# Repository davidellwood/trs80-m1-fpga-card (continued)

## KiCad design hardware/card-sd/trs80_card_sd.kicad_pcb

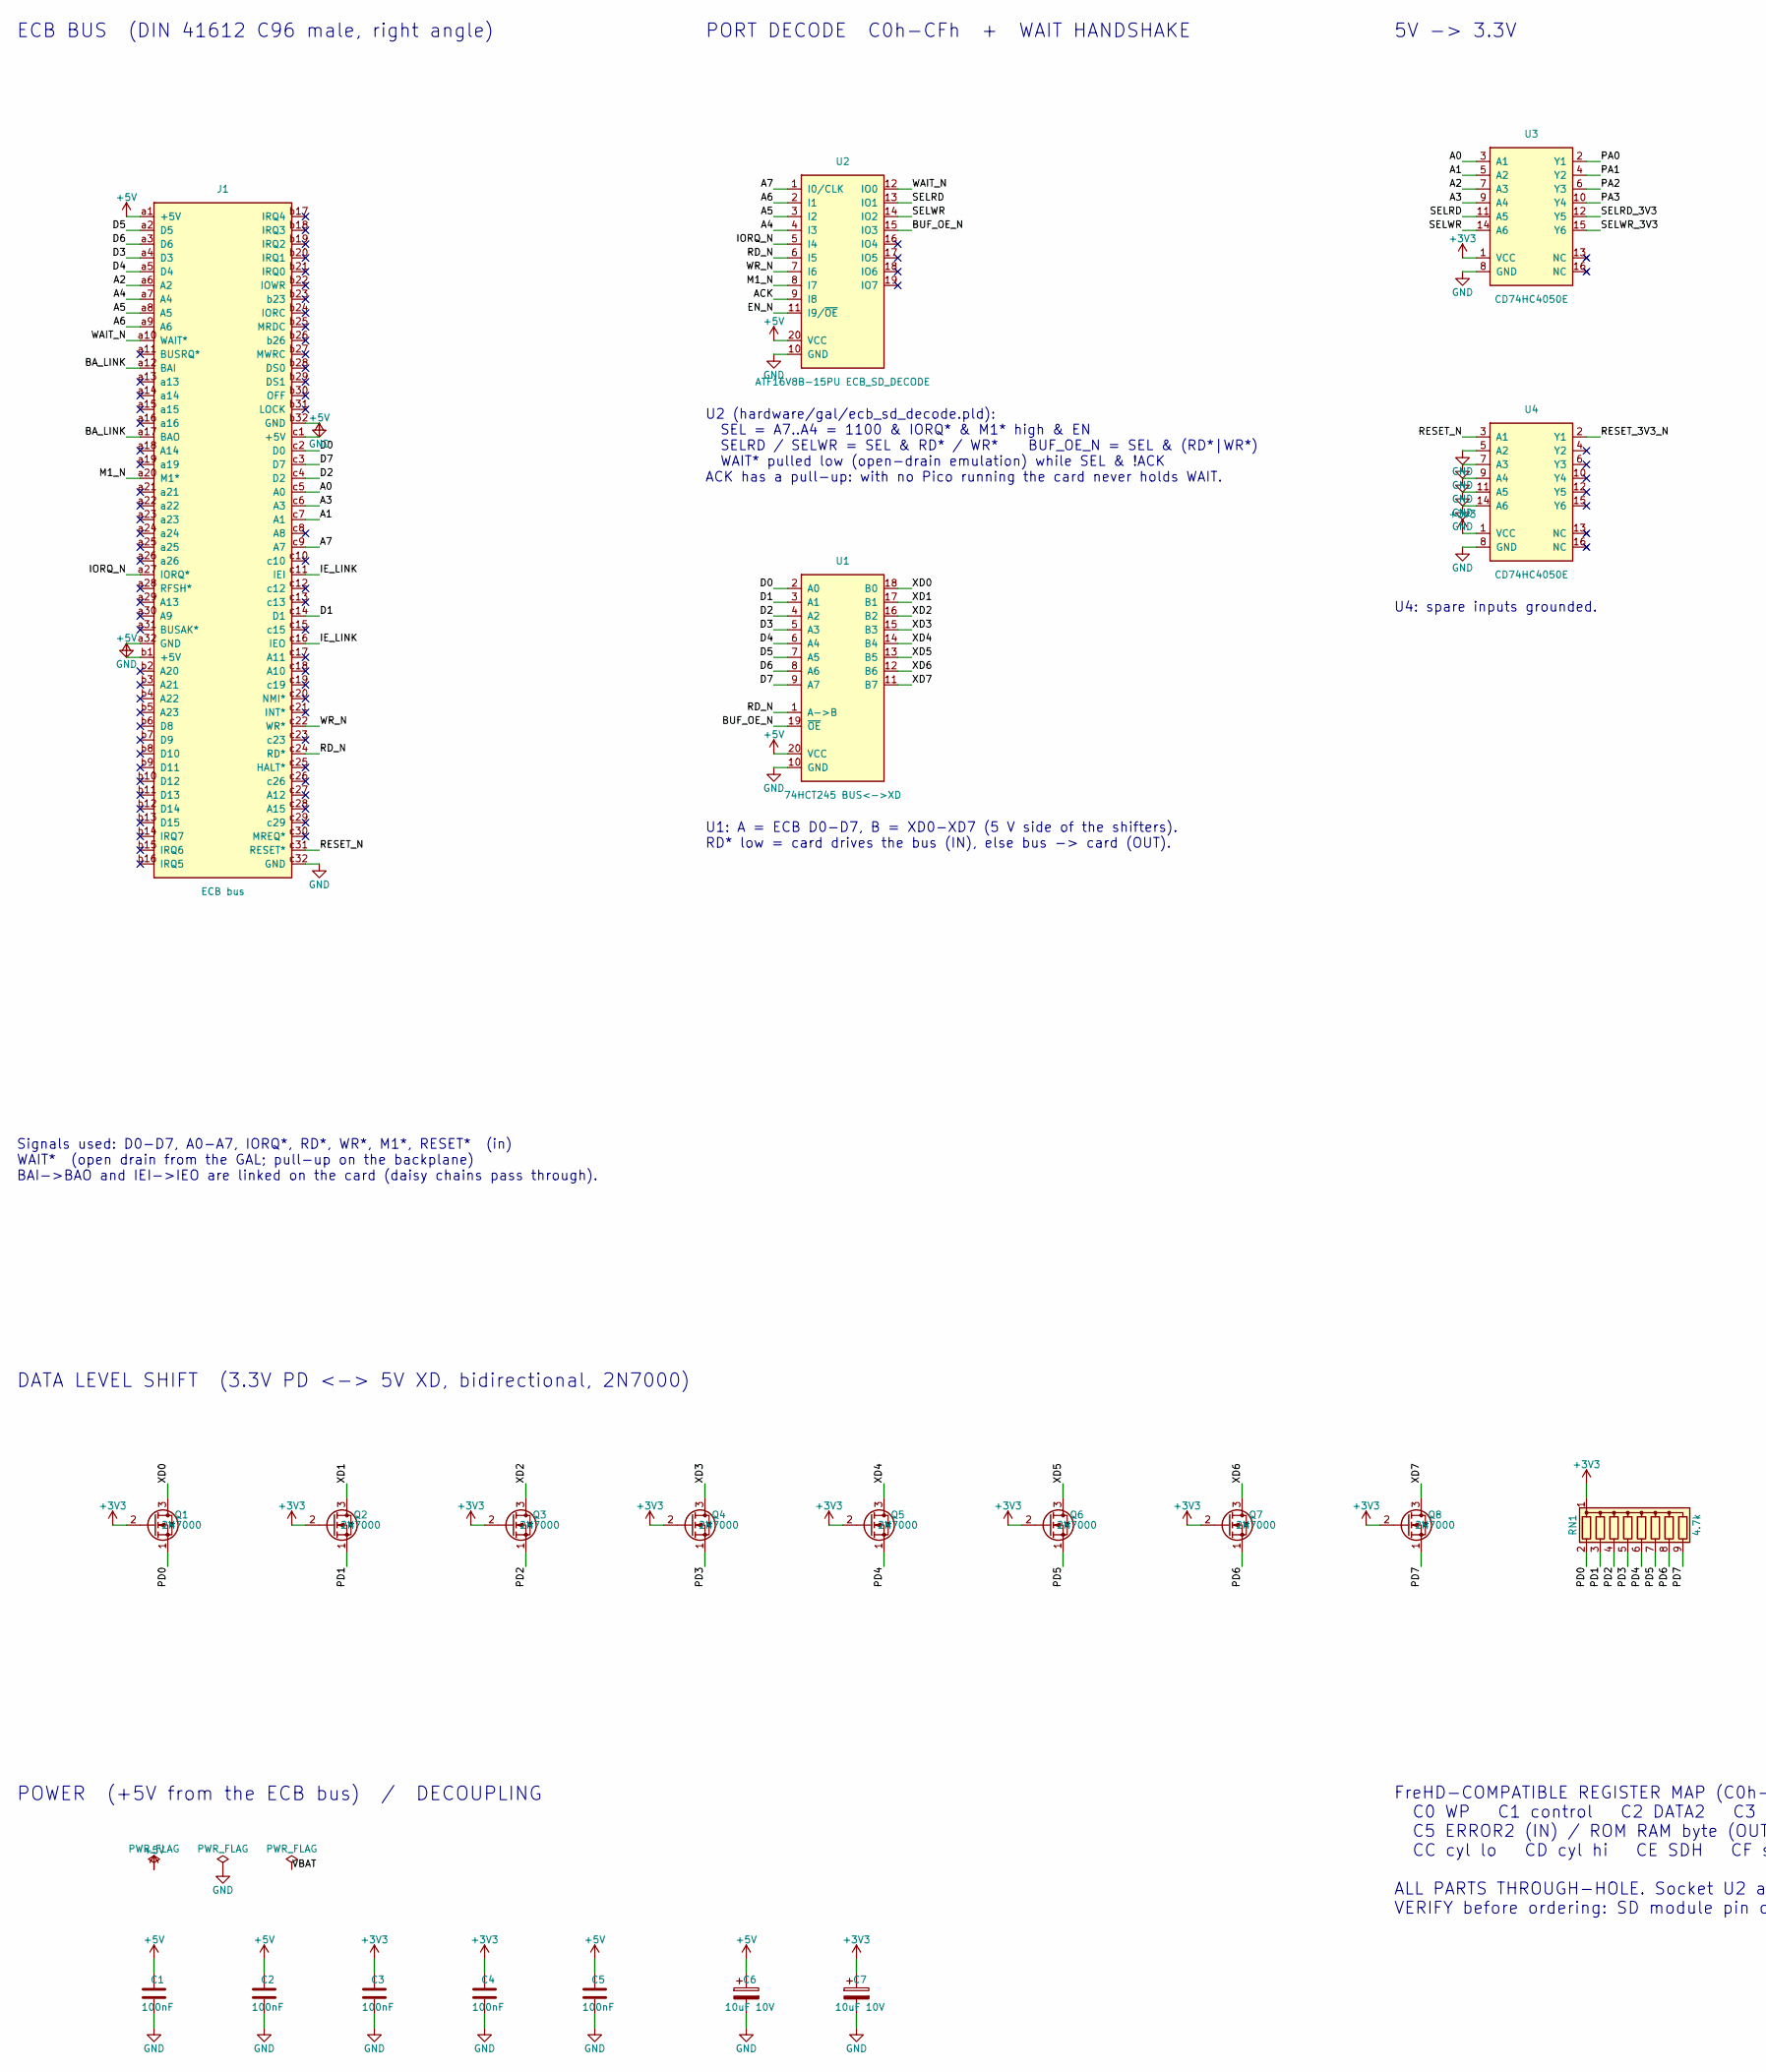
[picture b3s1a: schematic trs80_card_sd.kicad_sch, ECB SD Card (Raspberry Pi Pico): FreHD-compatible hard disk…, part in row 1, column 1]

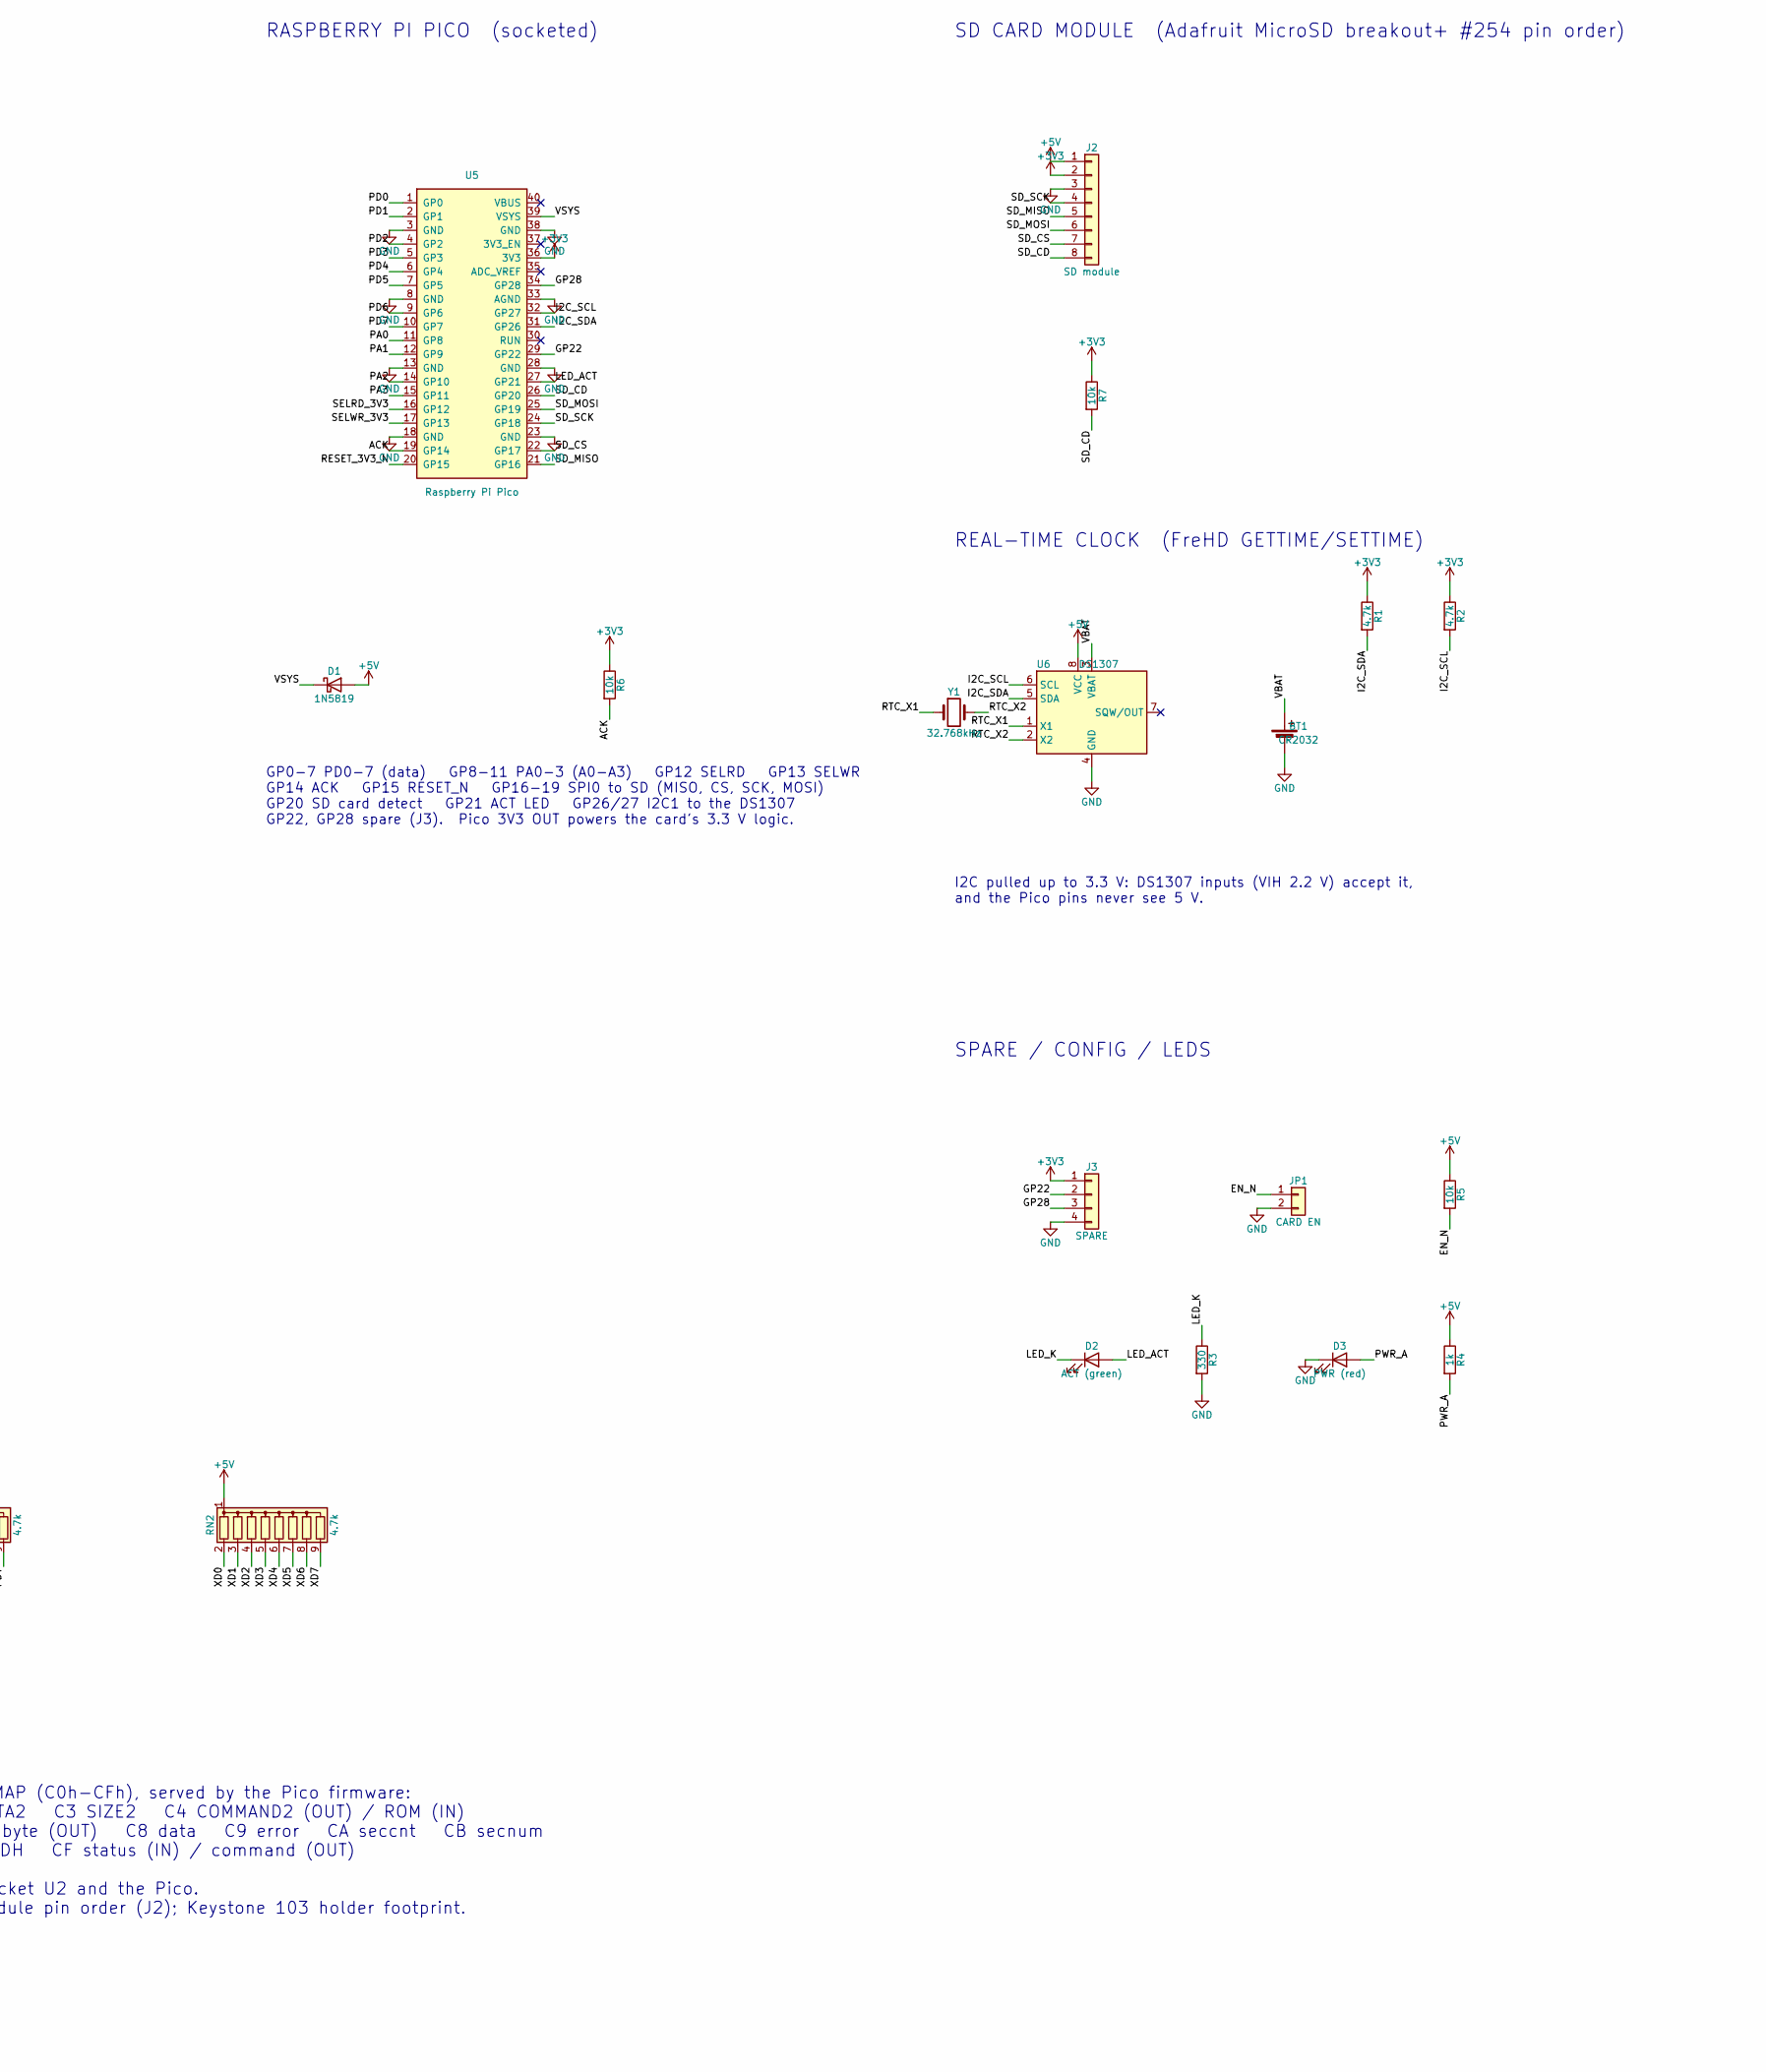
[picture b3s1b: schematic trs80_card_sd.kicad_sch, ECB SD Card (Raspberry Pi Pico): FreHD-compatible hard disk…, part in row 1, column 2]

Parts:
BT1: CR2032; BatteryHolder_Keystone_103_1x20mm
C1, C2, C3, C4, C5: 100nF; C_Disc_D5.0mm_W2.5mm_P5.00mm
C6, C7: 10uF 10V; CP_Radial_D5.0mm_P2.00mm
D1: 1N5819; D_DO-41_SOD81_P10.16mm_Horizontal
D2: ACT (green); LED_D3.0mm
D3: PWR (red); LED_D3.0mm
J1: ECB bus; DIN41612_C_3x32_Male_Horizontal_THT
J2: SD module; PinSocket_1x08_P2.54mm_Vertical
J3: SPARE; PinHeader_1x04_P2.54mm_Vertical
JP1: CARD EN; PinHeader_1x02_P2.54mm_Vertical
Q1, Q2, Q3, Q4, Q5, Q6, Q7, Q8: 2N7000; TO-92_Inline_Wide
R1, R2: 4.7k; R_Axial_DIN0207_L6.3mm_D2.5mm_P10.16mm_Horizontal
R3: 330; R_Axial_DIN0207_L6.3mm_D2.5mm_P10.16mm_Horizontal
R4: 1k; R_Axial_DIN0207_L6.3mm_D2.5mm_P10.16mm_Horizontal
R5, R6, R7: 10k; R_Axial_DIN0207_L6.3mm_D2.5mm_P10.16mm_Horizontal
RN1, RN2: 4.7k; R_Array_SIP9
U1: 74HCT245 BUS<->XD; DIP-20_W7.62mm
U2: ATF16V8B-15PU ECB_SD_DECODE; DIP-20_W7.62mm_Socket
U3, U4: CD74HC4050E; DIP-16_W7.62mm
U5: Raspberry Pi Pico; RaspberryPi_Pico_Common_THT
U6: DS1307; DIP-8_W7.62mm
Y1: 32.768kHz; Crystal_C26-LF_D2.1mm_L6.5mm_Horizontal

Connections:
+3V3: C3.1, C4.1, C7.1, J2.2, J3.1, Q1.2 (G), Q2.2 (G), Q3.2 (G), Q4.2 (G), Q5.2 (G), Q6.2 (G), Q7.2 (G), Q8.2 (G), R1.1, R2.1, R6.1, R7.1, RN1.1 (common), U3.1 (VCC), U4.1 (VCC), U5.36 (3V3)
+5V: C1.1, C2.1, C5.1, C6.1, D1.2 (A), J1.a1 (+5V), J1.b1 (+5V), J1.c1 (+5V), J2.1, R4.1, R5.1, RN2.1 (common), U1.20 (VCC), U2.20 (VCC), U6.8 (VCC)
/A0: J1.c5 (A0), U3.3 (A1)
/A1: J1.c7 (A1), U3.5 (A2)
/A2: J1.a6 (A2), U3.7 (A3)
/A3: J1.c6 (A3), U3.9 (A4)
/A4: J1.a7 (A4), U2.4 (I3)
/A5: J1.a8 (A5), U2.3 (I2)
/A6: J1.a9 (A6), U2.2 (I1)
/A7: J1.c9 (A7), U2.1 (I0/CLK)
/ACK: R6.2, U2.9 (I8), U5.19 (GP14)
/BA_LINK: J1.a12 (BAI), J1.a17 (BAO)
/BUF_OE_N: U1.19 (~OE), U2.15 (IO3)
/D0: J1.c2 (D0), U1.2 (A0)
/D1: J1.c14 (D1), U1.3 (A1)
/D2: J1.c4 (D2), U1.4 (A2)
/D3: J1.a4 (D3), U1.5 (A3)
/D4: J1.a5 (D4), U1.6 (A4)
/D5: J1.a2 (D5), U1.7 (A5)
/D6: J1.a3 (D6), U1.8 (A6)
/D7: J1.c3 (D7), U1.9 (A7)
/EN_N: JP1.1, R5.2, U2.11 (I9/~OE)
/GP22: J3.2, U5.29 (GP22)
/GP28: J3.3, U5.34 (GP28)
/I2C_SCL: R2.2, U5.32 (GP27), U6.6 (SCL)
/I2C_SDA: R1.2, U5.31 (GP26), U6.5 (SDA)
/IE_LINK: J1.c11 (IEI), J1.c16 (IEO)
/IORQ_N: J1.a27 (IORQ*), U2.5 (I4)
/LED_ACT: D2.2 (A), U5.27 (GP21)
/LED_K: D2.1 (K), R3.1
/M1_N: J1.a20 (M1*), U2.8 (I7)
/PA0: U3.2 (Y1), U5.11 (GP8)
/PA1: U3.4 (Y2), U5.12 (GP9)
/PA2: U3.6 (Y3), U5.14 (GP10)
/PA3: U3.10 (Y4), U5.15 (GP11)
/PD0: Q1.1 (S), RN1.2 (R1), U5.1 (GP0)
/PD1: Q2.1 (S), RN1.3 (R2), U5.2 (GP1)
/PD2: Q3.1 (S), RN1.4 (R3), U5.4 (GP2)
/PD3: Q4.1 (S), RN1.5 (R4), U5.5 (GP3)
/PD4: Q5.1 (S), RN1.6 (R5), U5.6 (GP4)
/PD5: Q6.1 (S), RN1.7 (R6), U5.7 (GP5)
/PD6: Q7.1 (S), RN1.8 (R7), U5.9 (GP6)
/PD7: Q8.1 (S), RN1.9 (R8), U5.10 (GP7)
/PWR_A: D3.2 (A), R4.2
/RD_N: J1.c24 (RD*), U1.1 (A->B), U2.6 (I5)
/RESET_3V3_N: U4.2 (Y1), U5.20 (GP15)
/RESET_N: J1.c31 (RESET*), U4.3 (A1)
/RTC_X1: U6.1 (X1), Y1.1
/RTC_X2: U6.2 (X2), Y1.2
/SD_CD: J2.8, R7.2, U5.26 (GP20)
/SD_CS: J2.7, U5.22 (GP17)
/SD_MISO: J2.5, U5.21 (GP16)
/SD_MOSI: J2.6, U5.25 (GP19)
/SD_SCK: J2.4, U5.24 (GP18)
/SELRD: U2.13 (IO1), U3.11 (A5)
/SELRD_3V3: U3.12 (Y5), U5.16 (GP12)
/SELWR: U2.14 (IO2), U3.14 (A6)
/SELWR_3V3: U3.15 (Y6), U5.17 (GP13)
/VBAT: BT1.1 (+), U6.3 (VBAT)
/VSYS: D1.1 (K), U5.39 (VSYS)
/WAIT_N: J1.a10 (WAIT*), U2.12 (IO0)
/WR_N: J1.c22 (WR*), U2.7 (I6)
/XD0: Q1.3 (D), RN2.2 (R1), U1.18 (B0)
/XD1: Q2.3 (D), RN2.3 (R2), U1.17 (B1)
/XD2: Q3.3 (D), RN2.4 (R3), U1.16 (B2)
/XD3: Q4.3 (D), RN2.5 (R4), U1.15 (B3)
/XD4: Q5.3 (D), RN2.6 (R5), U1.14 (B4)
/XD5: Q6.3 (D), RN2.7 (R6), U1.13 (B5)
/XD6: Q7.3 (D), RN2.8 (R7), U1.12 (B6)
/XD7: Q8.3 (D), RN2.9 (R8), U1.11 (B7)
GND: BT1.2 (-), C1.2, C2.2, C3.2, C4.2, C5.2, C6.2, C7.2, D3.1 (K), J1.a32 (GND), J1.b32 (GND), J1.c32 (GND), J2.3, J3.4, JP1.2, R3.2, U1.10 (GND), U2.10 (GND), U3.8 (GND), U4.5 (A2), U4.7 (A3), U4.8 (GND), U4.9 (A4), U4.11 (A5), U4.14 (A6), U5.3 (GND), U5.8 (GND), U5.13 (GND), U5.18 (GND), U5.23 (GND), U5.28 (GND), U5.33 (AGND), U5.38 (GND), U6.4 (GND)

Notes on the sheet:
ECB BUS (DIN 41612 C96 male, right angle)
Signals used: D0-D7, A0-A7, IORQ*, RD*, WR*, M1*, RESET* (in) WAIT* (open drain from the GAL; pull-up on the backplane) BAI->BAO and IEI->IEO are linked on the card (daisy chains pass through).
PORT DECODE C0h-CFh + WAIT HANDSHAKE
U2 (hardware/gal/ecb_sd_decode.pld): SEL = A7..A4 = 1100 & IORQ* & M1* high & EN SELRD / SELWR = SEL & RD* / WR* BUF_OE_N = SEL & (RD*|WR*) WAIT* pulled low (open-drain emulation) while SEL & !ACK ACK has a pull-up: with no Pico running the card never holds WAIT.
U1: A = ECB D0-D7, B = XD0-XD7 (5 V side of the shifters). RD* low = card drives the bus (IN), else bus -> card (OUT).
5V -> 3.3V
U4: spare inputs grounded.
DATA LEVEL SHIFT (3.3V PD <-> 5V XD, bidirectional, 2N7000)
RASPBERRY PI PICO (socketed)
GP0-7 PD0-7 (data) GP8-11 PA0-3 (A0-A3) GP12 SELRD GP13 SELWR GP14 ACK GP15 RESET_N GP16-19 SPI0 to SD (MISO, CS, SCK, MOSI) GP20 SD card detect GP21 ACT LED GP26/27 I2C1 to the DS1307 GP22, GP28 spare (J3). Pico 3V3 OUT powers the card's 3.3 V logic.
SD CARD MODULE (Adafruit MicroSD breakout+ #254 pin order)
REAL-TIME CLOCK (FreHD GETTIME/SETTIME)
I2C pulled up to 3.3 V: DS1307 inputs (VIH 2.2 V) accept it, and the Pico pins never see 5 V.
SPARE / CONFIG / LEDS
POWER (+5V from the ECB bus) / DECOUPLING
FreHD-COMPATIBLE REGISTER MAP (C0h-CFh), served by the Pico firmware: C0 WP C1 control C2 DATA2 C3 SIZE2 C4 COMMAND2 (OUT) / ROM (IN) C5 ERROR2 (IN) / ROM RAM byte (OUT) C8 data C9 error CA seccnt CB secnum CC cyl lo CD cyl hi CE SDH CF status (IN) / command (OUT) ALL PARTS THROUGH-HOLE. Socket U2 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

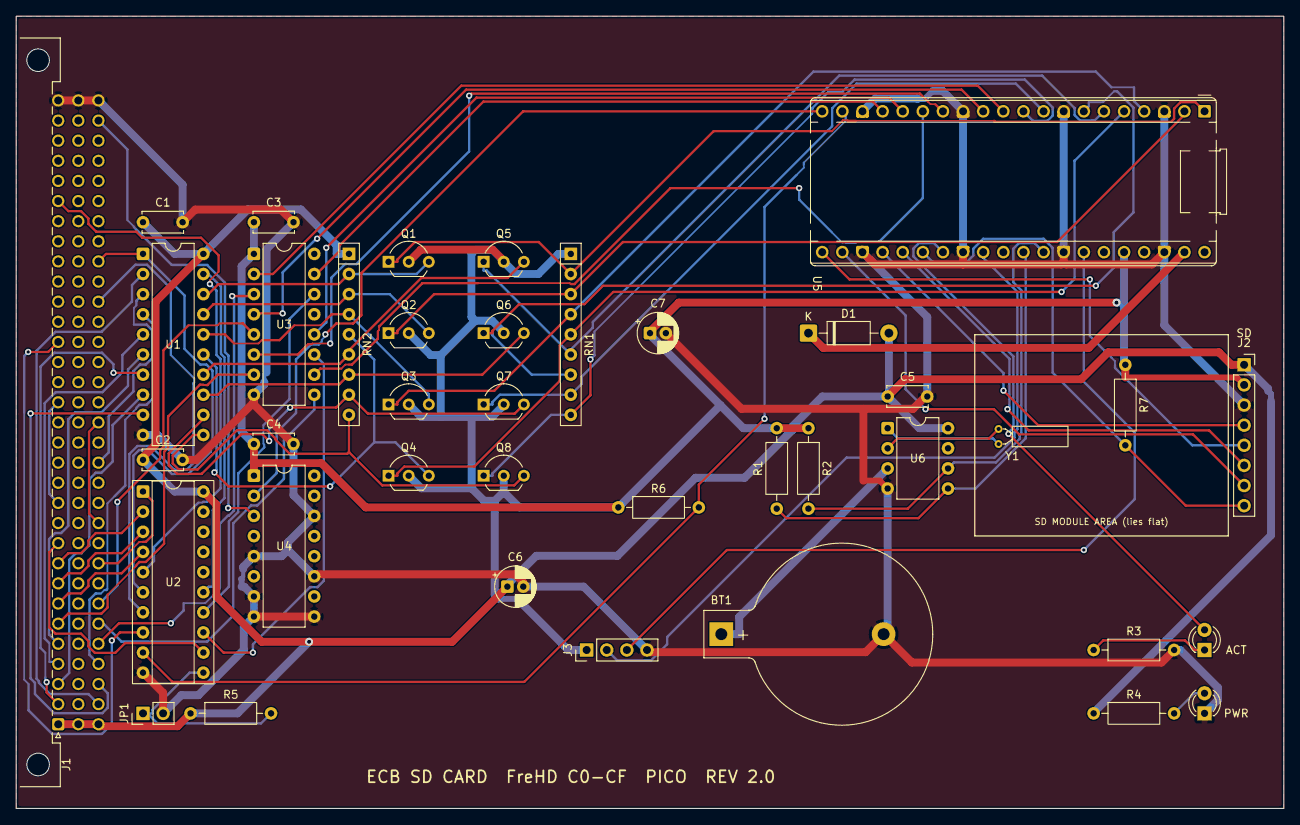
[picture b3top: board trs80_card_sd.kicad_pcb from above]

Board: 2 copper layers, 160.0 x 100.0 mm, 39 parts (0 on the bottom side), 71 nets.
